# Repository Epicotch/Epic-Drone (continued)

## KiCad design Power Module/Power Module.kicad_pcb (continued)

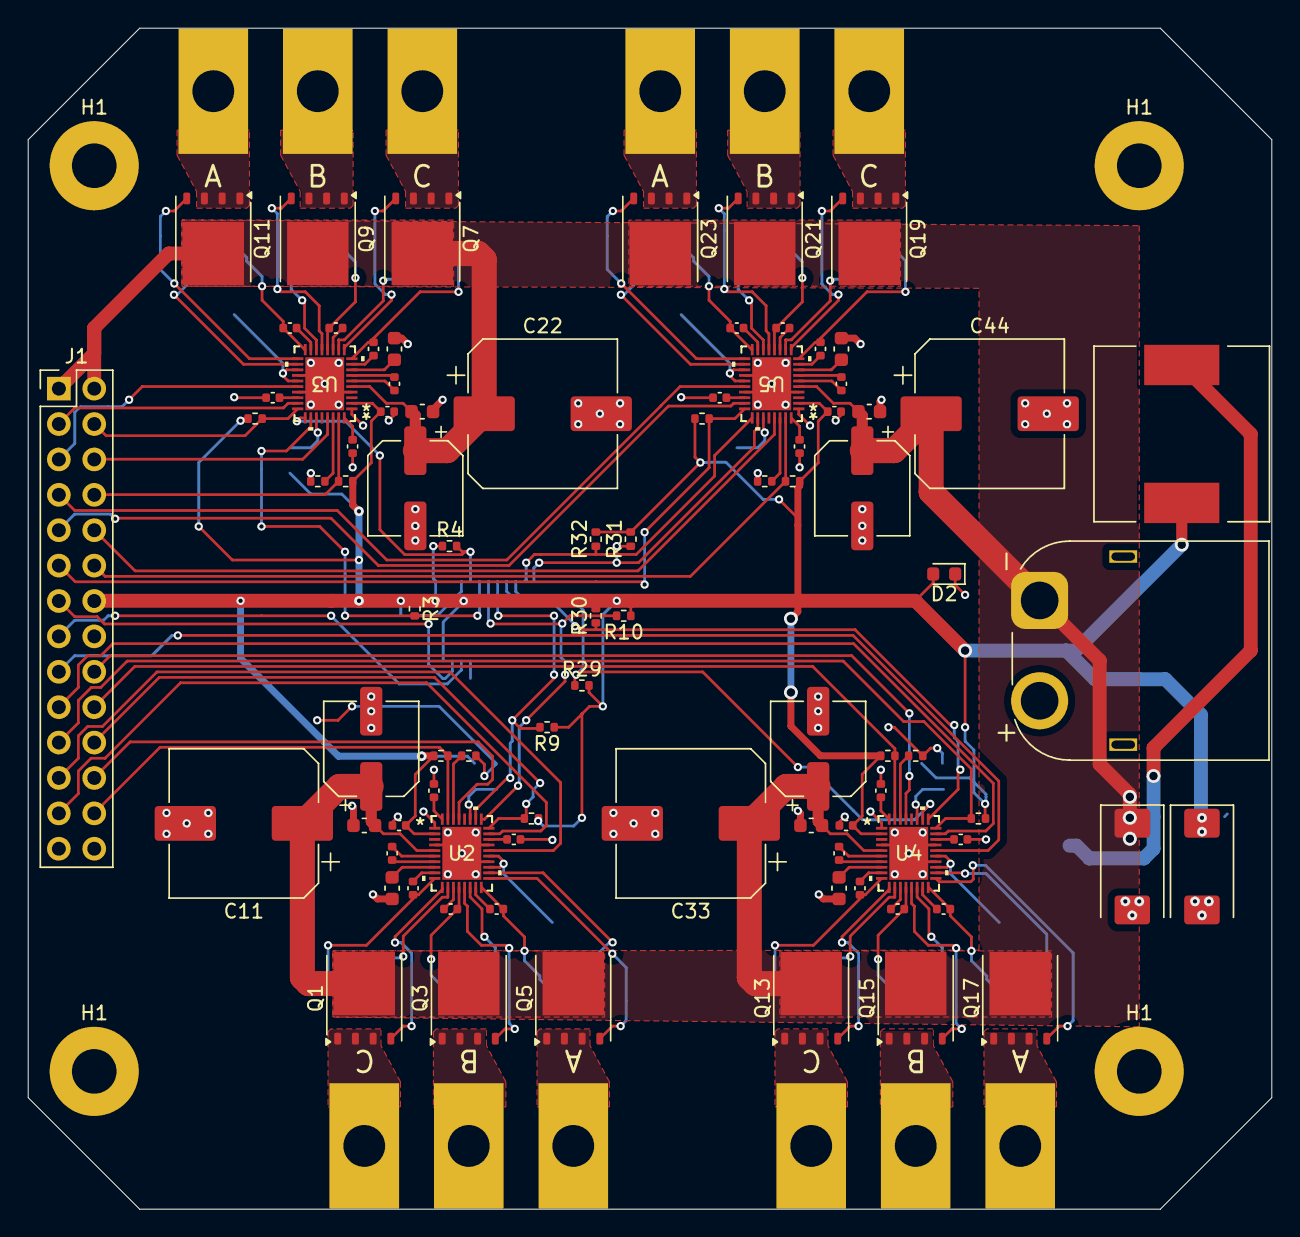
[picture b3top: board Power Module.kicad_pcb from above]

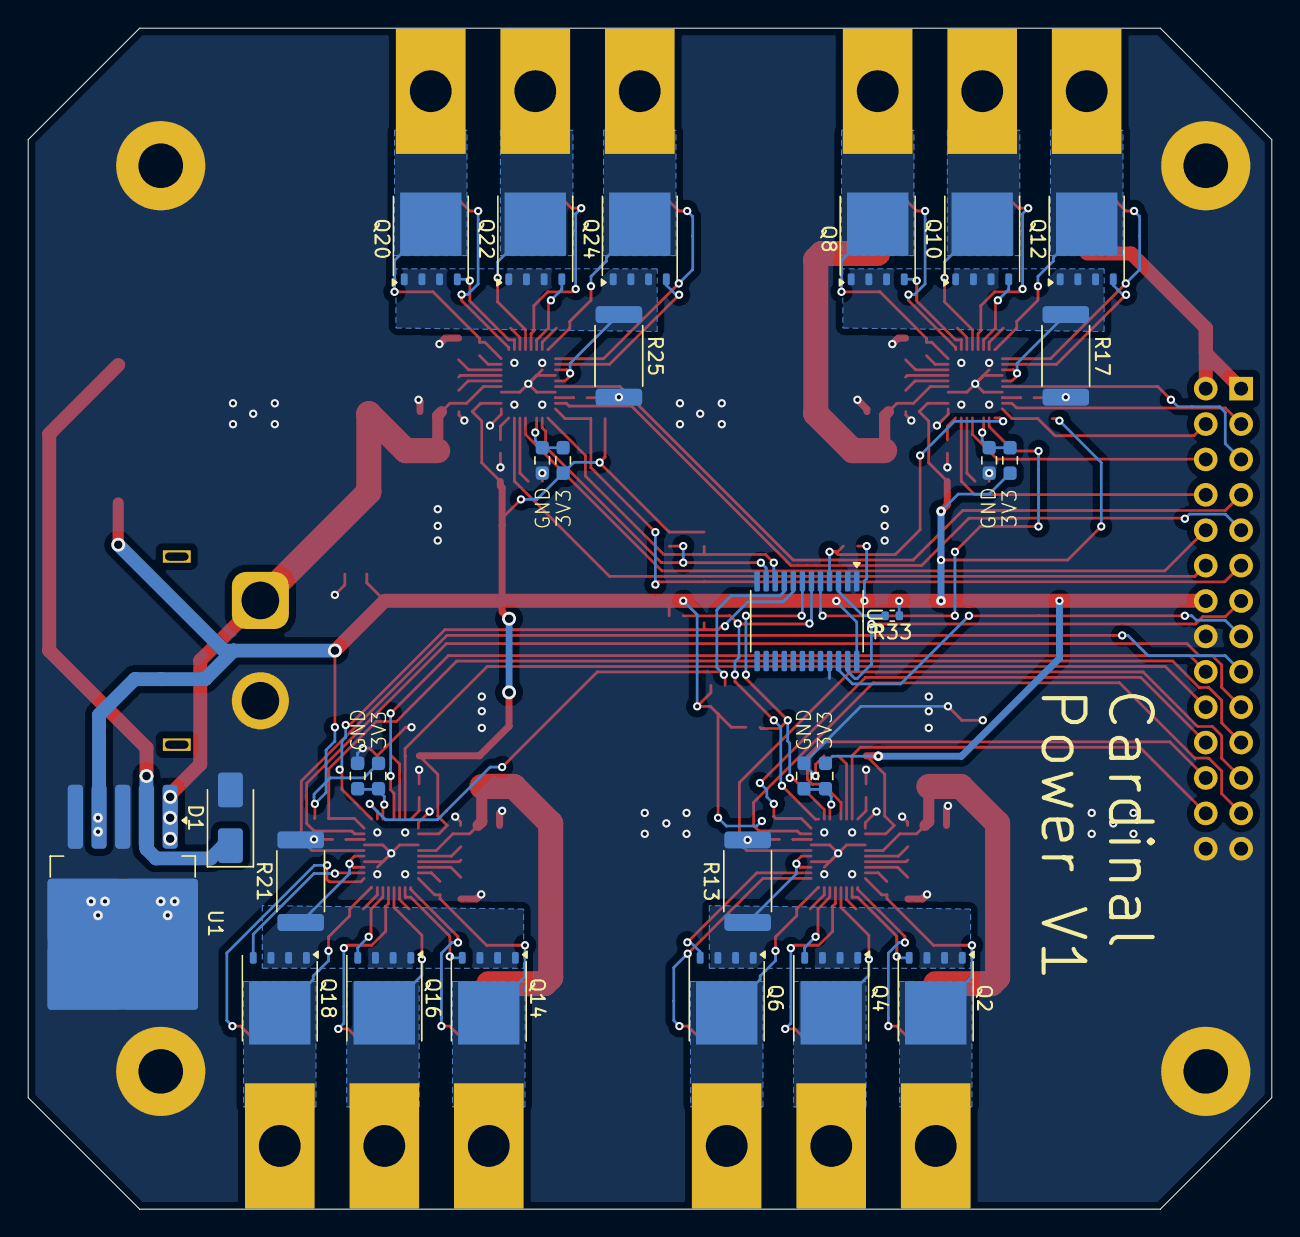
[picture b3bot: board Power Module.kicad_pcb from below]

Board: 2 copper layers, 89.2 x 84.8 mm, 122 parts (28 on the bottom side), 115 nets.

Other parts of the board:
H1#2, H1#3, H1#4: MountingHole_Pad; MountingHole_3.2mm_M3_Pad

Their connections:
AGND: H1#2.1, H1#3.1, H1#4.1; also elsewhere on the board

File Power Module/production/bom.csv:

Designator,Footprint,Quantity,Value,LCSC Part #
BT1,AMASS_XT60PW-M_1x02_P7.20mm_Horizontal,1,25V,
C1,CP_EIA-7343-30_AVX-N,1,1000uF,
"C10, C12, C13, C14, C15, C16, C21, C23, C24, C25, C26, C27, C3, C32, C34, C35, C36, C37, C38, C4, C43, C45, C46, C5",0402,24,1uF,
"C11, C22, C33, C44",CP_Elec_10x10.5,4,470uF,
"C17, C28, C39, C6",0603,4,10uF,
"C18, C29, C40, C7",0402,4,470nF,
"C19, C30, C41, C8",CP_Elec_6.3x7.7,4,47uF,
C2,0603,1,1000uF,
"C20, C31, C42, C9",0603,4,0.1uF,
C47,CP_EIA-7343-43_Kemet-X,1,100uF,
D1,D_SMA,1,SS33,
D2,0603,1,LED,
J1,PinHeader_2x14_P2.54mm_Vertical,1,Conn_02x14_Odd_Even,
"J2, J3, J4, J5",Edge_Solderpoint,4,MOTOR,
L1,L_12x12mm_H6mm,1,SMDRI127-151MT,
"Q1, Q10, Q11, Q12, Q13, Q14, Q15, Q16, Q17, Q18, Q19, Q2, Q20, Q21, Q22, Q23, Q24, Q3, Q4, Q5, Q6, Q7, Q8, Q9",TDSON-8-1,24,CSD18509Q5B,
"R1, R11, R12, R2, R5, R6, R7, R8",0603,8,0,
"R10, R14, R15, R16, R18, R19, R20, R22, R23, R24, R26, R27, R28, R29, R3, R30, R31, R32, R4, R9",0402,20,4.7k,
"R13, R17, R21, R25",2512,4,0.01,
U1,TO-263-5_TabPin3,1,LM2576S-3.3,
"U2, U3, U4, U5",WQFN36_REE_TEX,4,MCF8329A1IREER,
U6,TSSOP-24_4.4x7.8mm_P0.65mm,1,TCA9548APWR,

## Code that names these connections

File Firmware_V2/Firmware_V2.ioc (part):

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Mcu.Name=STM32H562RITx
Mcu.Package=LQFP64
Mcu.UserName=STM32H562RITx
PA0.Mode=Asynchronous
PA0.Signal=UART4_TX
PA1.Mode=Asynchronous
PA1.Signal=UART4_RX
PA13(JTMS/SWDIO).Mode=Serial_Wire
PA13(JTMS/SWDIO).Signal=DEBUG_JTMS-SWDIO
PA14(JTCK/SWCLK).Mode=Serial_Wire
PA14(JTCK/SWCLK).Signal=DEBUG_JTCK-SWCLK
PA2.Mode=Asynchronous
PA2.Signal=USART2_TX
PA3.Mode=Asynchronous
PA3.Signal=USART2_RX
PA5.Mode=Full_Duplex_Master
PA5.Signal=SPI1_SCK
PA6.Signal=S_TIM13_CH1
PA7.Signal=S_TIM14_CH1
PA8.Mode=I2C
PA8.Signal=I2C3_SCL
PA9.Mode=Asynchronous
PA9.Signal=USART1_TX
PB10.Mode=I2C
PB10.Signal=I2C2_SCL
PB12.Mode=I2C
PB12.Signal=I2C2_SDA
PB14.Mode=Hardware Flow Control (RS485)
PB14.Signal=UART4_DE
PB15.Mode=Asynchronous
PB15.Signal=USART1_RX
PB4(NJTRST).Mode=Full_Duplex_Master
PB4(NJTRST).Signal=SPI1_MISO
PB5.Mode=Full_Duplex_Master
PB5.Signal=SPI1_MOSI
PB6.Mode=I2C
PB6.Signal=I2C1_SCL
PB7.Mode=I2C
PB7.Signal=I2C1_SDA
PB8.Signal=S_TIM16_CH1
PC10.Mode=Asynchronous
PC10.Signal=USART3_TX
PC14-OSC32_IN(OSC32_IN).Mode=LSE-External-Oscillator
PC14-OSC32_IN(OSC32_IN).Signal=RCC_OSC32_IN
PC15-OSC32_OUT(OSC32_OUT).Mode=LSE-External-Oscillator
PC15-OSC32_OUT(OSC32_OUT).Signal=RCC_OSC32_OUT
PC2.Signal=S_TIM17_CH1
PC4.Mode=Asynchronous
PC4.Signal=USART3_RX
PC7.Mode=External_Trigger_bidirectional
PC7.Signal=DEBUG_TRGIO
PC9.Mode=I2C
PC9.Signal=I2C3_SDA
PH0-OSC_IN(PH0).Mode=HSE-External-Oscillator
PH0-OSC_IN(PH0).Signal=RCC_OSC_IN
PH1-OSC_OUT(PH1).Mode=HSE-External-Oscillator
PH1-OSC_OUT(PH1).Signal=RCC_OSC_OUT
RCC.HSE_VALUE=8000000
RCC.SYSCLKFreq_VALUE=64000000
RCC.SYSCLKSource=RCC_SYSCLKSOURCE_PLLCLK
board=custom

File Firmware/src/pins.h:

/**
 * 
 * Pin definitions
 * 
 */

#include <stdint.h>

// Motor PWM
const uint8_t MOTOR_1 = 2;
const uint8_t MOTOR_2 = 3;
const uint8_t MOTOR_3 = 4;
const uint8_t MOTOR_4 = 5;

// Motor controls
const uint8_t ENA_1 = 23;
const uint8_t ENA_2 = 24;
const uint8_t ENA_3 = 38;
const uint8_t ENA_4 = 22;

const uint8_t S_OX_1 = A7;
const uint8_t S_OX_2 = A6;
const uint8_t S_OX_3 = A17;
const uint8_t S_OX_4 = A16;

const uint8_t NFAULT_1 = 26;
const uint8_t NFAULT_2 = 31;
const uint8_t NFAULT_3 = 30;
const uint8_t NFAULT_4 = 27;

// Radio pins
const uint8_t RSSI = A15;
const uint8_t XBEE_RESET = 6;

// Servo control pins
const uint8_t SERVO_1 = 15;
const uint8_t SERVO_2 = 37;
const uint8_t SERVO_3 = 14;
const uint8_t SERVO_4 = 36;

// IMU control pins
const uint8_t IMU_RST = 33;
const uint8_t IMU_INT = 9;

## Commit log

2024-12-15 wpi <<< mit
2024-12-15 0 DRC errors wooooo
2025-01-02 V1 design
2025-01-03 Started writing firmware, implementing motor driver
2025-01-03 added gitignore
2025-01-03 Pin config stuff
2025-01-03 Changed gitignore
2025-01-03 doofus, also added I2C multiplexer stuff
2025-01-06 Added a bunch of initialization stuff (IMU, I2C, etc.)
2025-01-06 Localization beginnings
2025-01-07 More localization work
2025-01-07 Threadified the sensors
2025-01-09 Started kalman stuff
2025-01-10 Added state machine skeleton
2025-01-10 Cleaning stuff up
2025-05-05 Started STM32 based firmware
2025-05-06 added accel and gyro reads, configs, init, reset, data ready, read and write
